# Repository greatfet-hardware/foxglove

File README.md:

# Foxglove
an advanced level shifting GreatFET neighbor

Required KiCad dependency:

https://github.com/greatscottgadgets/gsg-kicad-lib

If you are using git, the preferred way to install gsg-kicad-lib is to use the
submodule:

```
git submodule init && git submodule update
```

## Level Shifting

Foxglove is useful for interfacing with external targets at variety of I/O
voltage levels using a wide variety of protocols including SPI, I2C, UART, and
JTAG.  Level shifting on bank A is performed by the NXP 74LVCH1T45GW,125
supporting external voltages from 1.2 V to 5 V.  Level shifting on bank B pins
is performed by the Lattice LFE5U-12F-6BG256C (ECP5) FPGA supporting external
voltages from 1.2 V to 3.3 V.  Bank B also supports differential signals such
as LVDS.

## Pin Multiplexing

The FPGA allows Foxglove to switch arbitrary external wires to a variety of
pins on the Azalea's microcontroller in order to support a wide range of
microcontroller peripherals.

## Measurement and Probing

Foxglove provides the ability to connect an ADC, DAC, comparator, pull-up
resistor, or pull-down resistor to any of the pins on bank A.  This allows
analog measurement and probing of external targets.

Additionally, Foxglove is very useful for digital logic analysis and pattern
generation.

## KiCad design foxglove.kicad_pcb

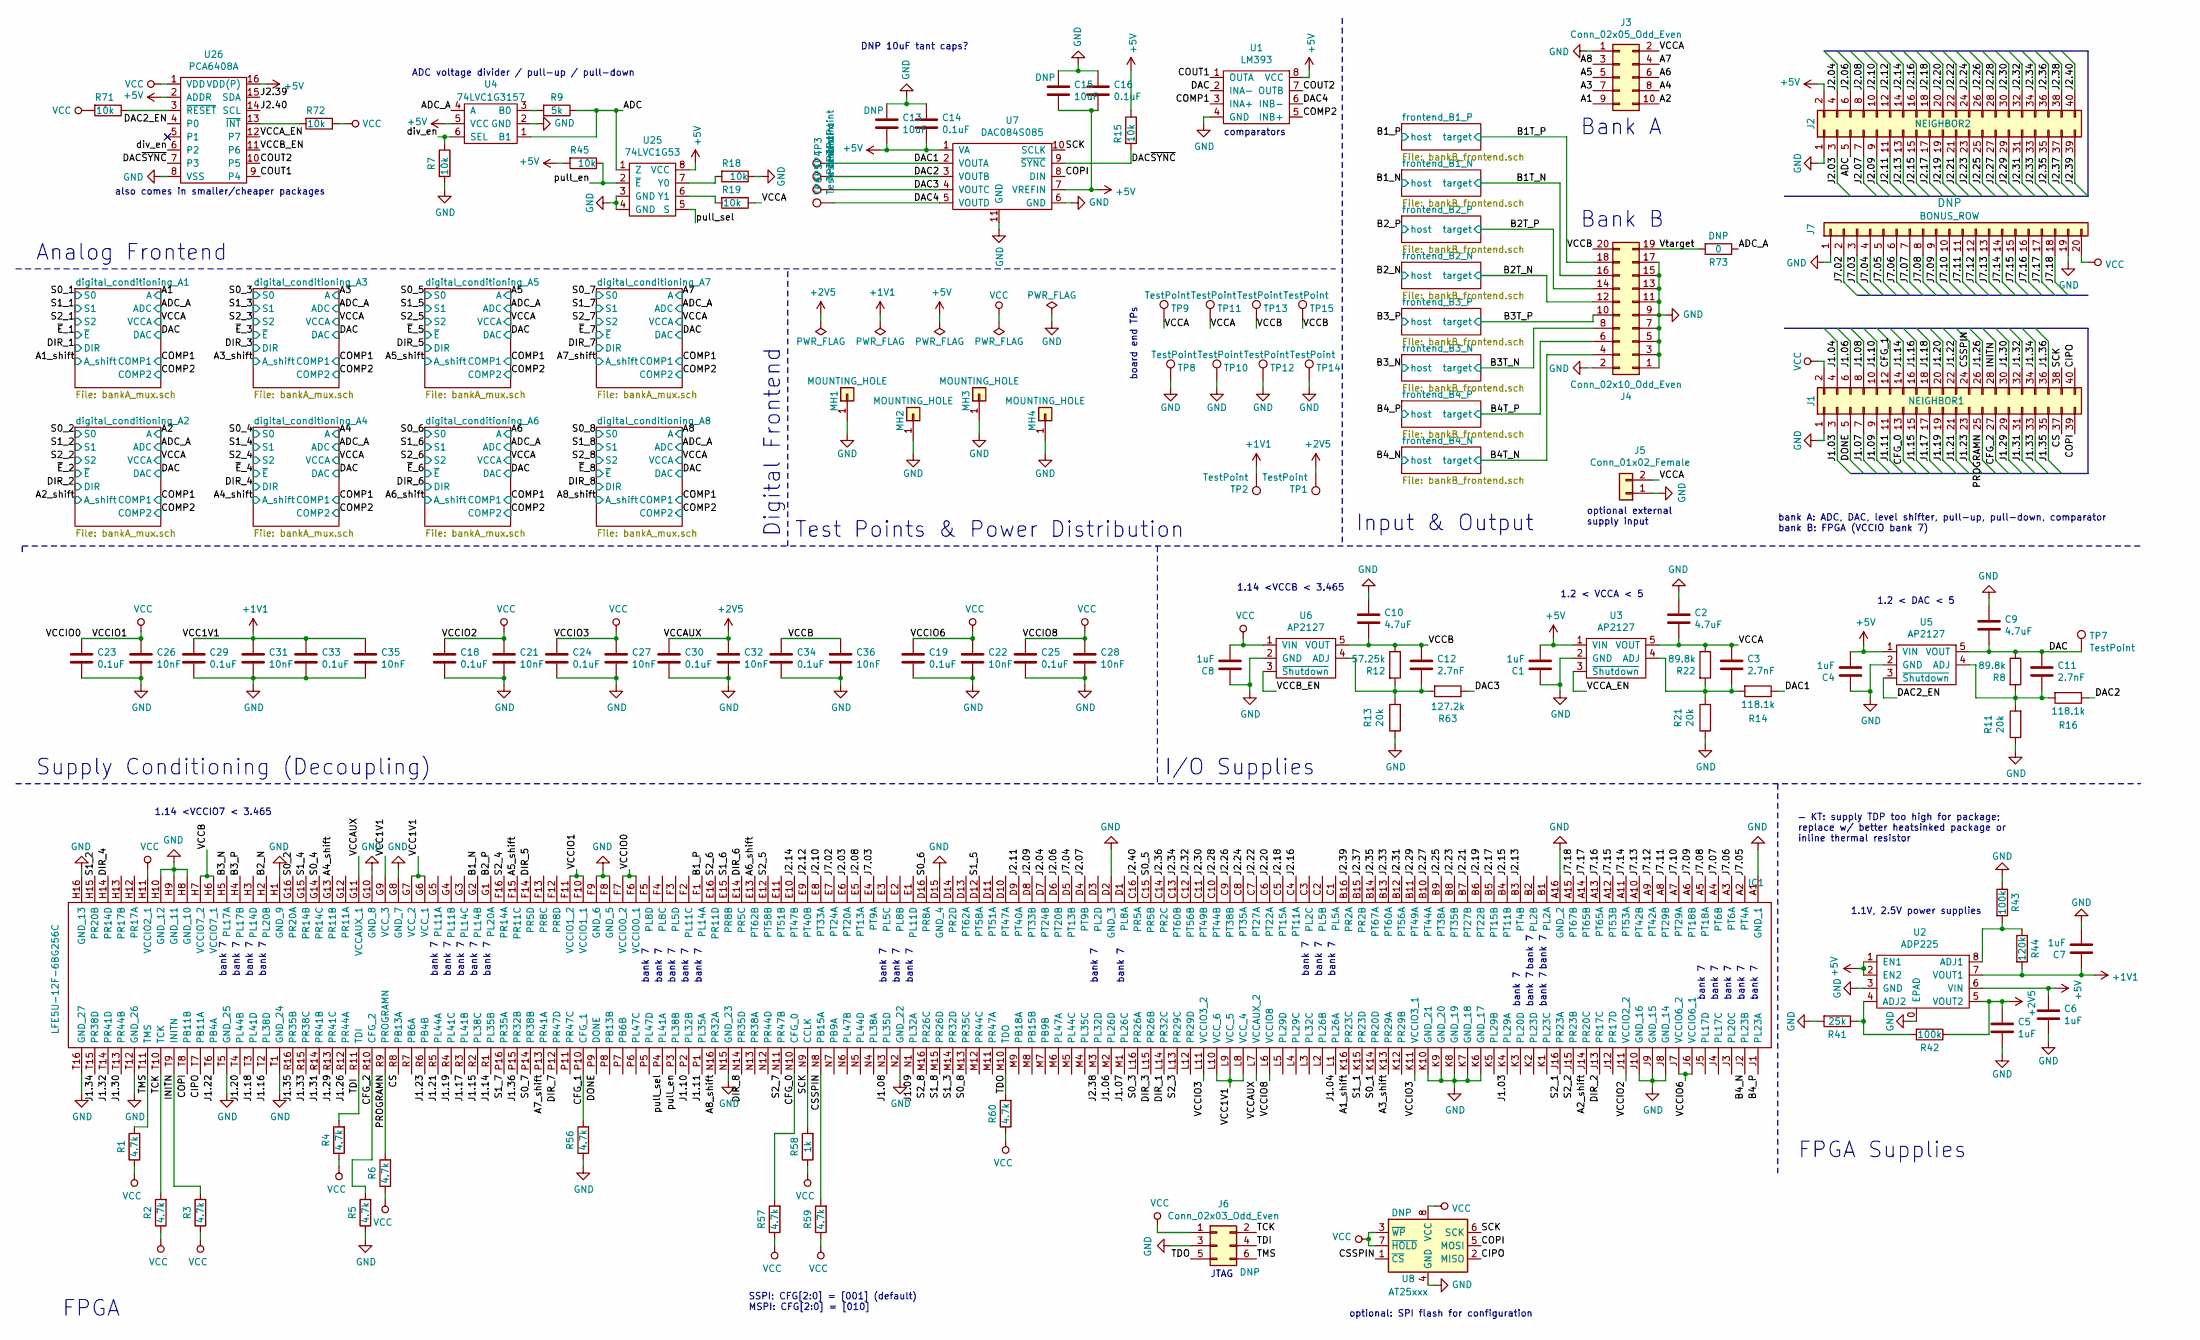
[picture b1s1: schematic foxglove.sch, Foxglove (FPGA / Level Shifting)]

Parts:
C1, C4, C5, C6, C7, C8: 1uF; 0402; Part Number GRT155R61E105KE01D
C2, C9, C10: 4.7uF; 0402; Part Number GRM155R61A475MEAAD
C3, C11, C12: 2.7nF; 0402; Part Number CC0402KRX7R9BB272
C13, C15: 10uF; 0603; Part Number F981A106MMA
C14, C16, C18, C19, C23, C24, C25, C29, C30, C33, C34: 0.1uF; 0402; Part Number EMK105BJ104KV-F
C21, C22, C26, C27, C28, C31, C32, C35, C36: 10nF; 0402; Part Number CL05B103KO5NNNC
IC1: LFE5U-12F-6BG256C; BGA256C80P16X16_1400X1400X170; Part Number LFE5U-12F-6BG256C; Mouser Part Number 842-LFE5U12F6BG256C
J1: NEIGHBOR1; HEADER-2x20; Part Number SSQ-120-23-G-D
J2: NEIGHBOR2; HEADER-2x20; Part Number SSQ-120-23-G-D
J3: Conn_02x05_Odd_Even; PinHeader_2x05_P2.54mm_Vertical; Part Number SBH11-PBPC-D05-RA-BK
J4: Conn_02x10_Odd_Even; PinHeader_2x10_P2.54mm_Vertical; Part Number SBH11-PBPC-D10-RA-BK
J5: Conn_01x02_Female; HEADER-1x2
J6: Conn_02x03_Odd_Even; PinHeader_2x03_P1.00mm_Vertical_SMD
J7: BONUS_ROW; HEADER-1x20; Part Number SSQ-120-23-G-S
MH1, MH2, MH3, MH4: MOUNTING_HOLE; HOLE126MIL-COPPER
R1, R2, R3, R4, R5, R6, R56, R57, R59, R60: 4.7k; 0402; Part Number RMCF0402JT4K70
R7, R15, R18, R19, R45, R71, R72: 10k; 0402; Part Number RMCF0402JT10K0
R8, R22: 89.8k; 0402; Part Number RMCF0402FT88K7
R9: 5k; 0402; Part Number PNM0402E5001BST1
R11, R13, R21: 20k; 0402; Part Number RMCF0402JT20K0
R12: 57.25k; 0402; Part Number RMCF0402FT57K6
R14, R16: 118.1k; 0402; Part Number RMCF0402FT118K
R41: 25k; 0402; Part Number PNM0402E2502BST1
R42, R43: 100k; 0402; Part Number RMCF0402JT100K
R44: 120k; 0402; Part Number RMCF0402FT120K
R58: 1k; 0402; Part Number RK73B1ETTP102J
R63: 127.2k; 0402; Part Number RMCF0402FT127K
R73: 0; 0402
TP1, TP2, TP3, TP4, TP5, TP6, TP7: TestPoint; TESTPOINT-50MIL
TP8, TP10, TP12, TP14: TestPoint; HEADER-1x1
TP9, TP11, TP13, TP15: TestPoint; HEADER-1x1-TESTPROBE
U1: LM393; SOIC8-154; Part Number LM393EDR2G
U2: ADP225; SON50P200X200X60-9N; Part Number ADP225ACPZ-R7
U3, U5, U6: AP2127; SOT-23-5; Part Number AP2127K-ADJTRG1
U4: 74LVC1G3157; SOT363; Part Number 74LVC1G3157DW-7
U7: DAC084S085; WSON-10-1EP_4x3mm_P0.5mm_EP2.2x2mm; Part Number DAC084S085CISDX/NOPB
U8: AT25xxx; SOIC8-154
U25: 74LVC1G53; VSSOP-8_2.3x2mm_P0.5mm; Part Number 74LVC1G53DC,125
U26: PCA6408A; TSSOP16; Part Number PCA6408APW,118

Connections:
+1V1: C7.1, C29.1, C31.1, C33.1, C35.1, IC1.G6 (VCC_1), IC1.G7 (VCC_2), IC1.G9 (VCC_3), IC1.L8 (VCC_4), IC1.L9 (VCC_5), IC1.L10 (VCC_6), R44.2, TP2.1, U2.7 (VOUT1)
+2V5: C5.1, C30.1, C32.1, IC1.G11 (VCCAUX_1), IC1.L7 (VCCAUX_2), R42.1, TP1.1, U2.5 (VOUT2)
+5V: C1.2, C4.2, C6.1, C13.1, C14.2, C15.1, C16.2, J2.2, R15.1, R45.2, U1.8 (VCC), U2.1 (EN1), U2.2 (EN2), U2.6 (VIN), U3.1 (VIN), U4.5 (VCC), U5.1 (VIN), U7.1 (VA), U7.7 (VREFIN), U25.8 (VCC), U26.2 (ADDR), U26.16 (VDD(P)); also elsewhere on the board
/A1_shift: IC1.K16 (PR23C); also elsewhere on the board
/A2: J3.10; also elsewhere on the board
/A2_shift: IC1.J14 (PR20C); also elsewhere on the board
/A3: J3.7; also elsewhere on the board
/A3_shift: IC1.K13 (PR29A); also elsewhere on the board
/A4_shift: IC1.G13 (PR11B); also elsewhere on the board
/A5: J3.5; also elsewhere on the board
/A5_shift: IC1.F15 (PR11C); also elsewhere on the board
/A6: J3.6; also elsewhere on the board
/A6_shift: IC1.E13 (PT62B); also elsewhere on the board
/A7: J3.4; also elsewhere on the board
/A7_shift: IC1.P13 (PR41A); also elsewhere on the board
/A8: J3.3; also elsewhere on the board
/A8_shift: IC1.N16 (PR32A); also elsewhere on the board
/ADC: J2.5, R9.1, U4.1 (B1), U25.1 (Z)
/ADC_A: R73.1, U4.4 (A); also elsewhere on the board
/B1T_N: J4.16; also elsewhere on the board
/B1T_P: J4.18; also elsewhere on the board
/B1_N: IC1.G2 (PL14B); also elsewhere on the board
/B1_P: IC1.F1 (PL14A); also elsewhere on the board
/B2T_N: J4.12; also elsewhere on the board
/B2T_P: J4.14; also elsewhere on the board
/B2_N: IC1.H2 (PL20B); also elsewhere on the board
/B2_P: IC1.G1 (PL20A); also elsewhere on the board
/B3T_N: J4.8; also elsewhere on the board
/B3T_P: J4.10; also elsewhere on the board
/B3_N: IC1.H5 (PL17A); also elsewhere on the board
/B3_P: IC1.H4 (PL17B); also elsewhere on the board
/B4T_N: J4.4; also elsewhere on the board
/B4T_P: J4.6; also elsewhere on the board
/B4_N: IC1.J2 (PL23B); also elsewhere on the board
/B4_P: IC1.J1 (PL23A); also elsewhere on the board
/CFG_0: IC1.N10 (CFG_0), J1.13, R57.2
/CFG_1: IC1.P10 (CFG_1), J1.12, R56.2
/CFG_2: IC1.R10 (CFG_2), J1.27, R5.2
/CIPO: IC1.T7 (PB11A), J1.40, U8.2 (MISO)
/COMP1: U1.3 (INA+); also elsewhere on the board
/COMP2: U1.5 (INB+); also elsewhere on the board
/COPI: IC1.T8 (PB11B), J1.39, U7.8 (DIN), U8.5 (MOSI)
/COUT1: U1.1 (OUTA), U26.9 (P4)
/COUT2: U1.7 (OUTB), U26.10 (P5)
/CS: IC1.R8 (PB13A), J1.37
/CSSPIN: IC1.N8 (PB15A), J1.24, R59.2, U8.1 (~CS)
/DAC: C9.2, C11.1, R8.1, TP7.1, U1.2 (INA-), U5.5 (VOUT); also elsewhere on the board
/DAC1: R14.1, TP3.1, U7.2 (VOUTA)
/DAC2: R16.1, TP4.1, U7.3 (VOUTB)
/DAC2_EN: U5.3 (~Shutdown~), U26.4 (P0)
/DAC3: R63.1, TP5.1, U7.4 (VOUTC)
/DAC4: TP6.1, U1.6 (INB-), U7.5 (VOUTD)
/DAC~SYNC~: R15.2, U7.9 (~SYNC~), U26.7 (P3)
/DIR_1: IC1.L14 (PR32C); also elsewhere on the board
/DIR_2: IC1.J13 (PR17C); also elsewhere on the board
/DIR_3: IC1.L15 (PR26B); also elsewhere on the board
/DIR_4: IC1.H14 (PR14D); also elsewhere on the board
/DIR_5: IC1.F14 (PR5D); also elsewhere on the board
/DIR_6: IC1.E14 (PR5C); also elsewhere on the board
/DIR_7: IC1.P12 (PR47D); also elsewhere on the board
/DIR_8: IC1.N14 (PR35D); also elsewhere on the board
/DONE: IC1.P9 (DONE), J1.5
/INITN: IC1.T9 (INITN), J1.28, R3.2
/J1.03: IC1.K4 (PL29A), J1.3
/J1.04: IC1.L1 (PL26A), J1.4
/J1.06: IC1.M2 (PL26D), J1.6
/J1.07: IC1.M1 (PL26C), J1.7
/J1.08: IC1.N3 (PL35D), J1.8
/J1.09: IC1.N1 (PL32A), J1.9
/J1.10: IC1.P2 (PL32B), J1.10
/J1.11: IC1.P1 (PL35A), J1.11
/J1.14: IC1.R1 (PL35B), J1.14
/J1.15: IC1.R2 (PL38C), J1.15
/J1.16: IC1.T2 (PL38D), J1.16
/J1.17: IC1.R3 (PL41B), J1.17
/J1.18: IC1.T3 (PL41D), J1.18
/J1.19: IC1.R4 (PL41C), J1.19
/J1.20: IC1.T4 (PL44B), J1.20
/J1.21: IC1.R5 (PL44A), J1.21
/J1.22: IC1.T6 (PB4A), J1.22
/J1.23: IC1.R6 (PB4B), J1.23
/J1.26: IC1.R12 (PR44A), J1.26
/J1.29: IC1.R13 (PR41C), J1.29
/J1.30: IC1.T13 (PR44B), J1.30
/J1.31: IC1.R14 (PR41B), J1.31
/J1.32: IC1.T14 (PR41D), J1.32
/J1.33: IC1.R15 (PR38C), J1.33
/J1.34: IC1.T15 (PR38D), J1.34
/J1.35: IC1.R16 (PR35B), J1.35
/J1.36: IC1.P15 (PR32B), J1.36
/J2.03: IC1.E6 (PT20A), J2.3
/J2.04: IC1.D7 (PT24B), J2.4
/J2.06: IC1.D6 (PT20B), J2.6
/J2.07: IC1.D4 (PT9B), J2.7
/J2.08: IC1.E5 (PT13A), J2.8
/J2.09: IC1.D8 (PT33B), J2.9
/J2.10: IC1.E8 (PT33A), J2.10
/J2.11: IC1.D9 (PT40A), J2.11
/J2.12: IC1.E9 (PT40B), J2.12
/J2.13: IC1.B3 (PT4B), J2.13
/J2.14: IC1.E10 (PT47B), J2.14
/J2.15: IC1.B4 (PT11B), J2.15
/J2.16: IC1.C4 (PT11A), J2.16
/J2.17: IC1.B5 (PT15B), J2.17
/J2.18: IC1.C5 (PT15A), J2.18
/J2.19: IC1.B6 (PT22B), J2.19
/J2.20: IC1.C6 (PT22A), J2.20
/J2.21: IC1.B7 (PT27B), J2.21
/J2.22: IC1.C7 (PT27A), J2.22
/J2.23: IC1.B8 (PT35B), J2.23
/J2.24: IC1.C8 (PT35A), J2.24
/J2.25: IC1.B9 (PT38A), J2.25
/J2.26: IC1.C9 (PT38B), J2.26
/J2.27: IC1.B10 (PT44A), J2.27
/J2.28: IC1.C10 (PT44B), J2.28
/J2.29: IC1.B11 (PT49A), J2.29
/J2.30: IC1.C11 (PT49B), J2.30
/J2.31: IC1.B12 (PT56A), J2.31
/J2.32: IC1.C12 (PT56B), J2.32
/J2.33: IC1.B13 (PT60A), J2.33
/J2.34: IC1.C13 (PT60B), J2.34
/J2.35: IC1.B14 (PT67A), J2.35
/J2.36: IC1.C14 (PR2C), J2.36
/J2.37: IC1.B15 (PR2B), J2.37
/J2.38: IC1.M3 (PL32D), J2.38
/J2.39: IC1.B16 (PR2A), J2.39, U26.15 (SDA)
/J2.40: IC1.C16 (PR5A), J2.40, U26.14 (SCL)
/J7.02: IC1.E7 (PT24A), J7.2
/J7.03: IC1.E4 (PT9A), J7.3
/J7.04: IC1.D5 (PT13B), J7.4
/J7.05: IC1.A2 (PT4A), J7.5
/J7.06: IC1.A3 (PT6A), J7.6
/J7.07: IC1.A4 (PT6B), J7.7
/J7.08: IC1.A5 (PT18A), J7.8
/J7.09: IC1.A6 (PT18B), J7.9
/J7.10: IC1.A7 (PT29A), J7.10
/J7.11: IC1.A8 (PT29B), J7.11
/J7.12: IC1.A9 (PT42A), J7.12
/J7.13: IC1.A10 (PT42B), J7.13
/J7.14: IC1.A11 (PT53A), J7.14
/J7.15: IC1.A12 (PT53B), J7.15
/J7.16: IC1.A13 (PT65A), J7.16
/J7.17: IC1.A14 (PT65B), J7.17
/J7.18: IC1.A15 (PT67B), J7.18
/PROGRAMN: IC1.R9 (PROGRAMN), J1.25, R6.2
/S0_1: IC1.K14 (PR20D); also elsewhere on the board
/S0_2: IC1.G16 (PR20A); also elsewhere on the board
/S0_3: IC1.L16 (PR26A); also elsewhere on the board
/S0_4: IC1.G14 (PR14C); also elsewhere on the board
/S0_5: IC1.C15 (PR5B); also elsewhere on the board
/S0_6: IC1.D16 (PR8A); also elsewhere on the board
/S0_7: IC1.P14 (PR38B); also elsewhere on the board
/S0_8: IC1.M13 (PR35C); also elsewhere on the board
/S1_1: IC1.K15 (PR23D); also elsewhere on the board
/S1_2: IC1.H15 (PR20B); also elsewhere on the board
/S1_3: IC1.M14 (PR32D); also elsewhere on the board
/S1_4: IC1.G15 (PR14B); also elsewhere on the board
/S1_5: IC1.D12 (PT58A); also elsewhere on the board
/S1_6: IC1.E15 (PR8B); also elsewhere on the board
/S1_7: IC1.P16 (PR35A); also elsewhere on the board
/S1_8: IC1.M15 (PR26D); also elsewhere on the board
/S2_1: IC1.J16 (PR23A); also elsewhere on the board
/S2_2: IC1.J15 (PR23B); also elsewhere on the board
/S2_3: IC1.L13 (PR29C); also elsewhere on the board
/S2_4: IC1.F16 (PR14A); also elsewhere on the board
/S2_5: IC1.E12 (PT58B); also elsewhere on the board
/S2_6: IC1.E16 (PR11D); also elsewhere on the board
/S2_7: IC1.N11 (PR47B); also elsewhere on the board
/S2_8: IC1.M16 (PR26C); also elsewhere on the board
/SCK: IC1.N9 (CCLK), J1.38, R58.2, U7.10 (SCLK), U8.6 (SCK)
/TCK: IC1.T10 (TCK), J6.2, R2.2
/TDI: IC1.R11 (TDI), J6.4, R4.2
/TDO: IC1.M10 (TDO), J6.5, R60.2
/TMS: IC1.T11 (TMS), J6.6, R1.2
/VCCA: C2.2, C3.1, J3.2, J5.2, R19.1, R22.1, TP9.1, TP11.1, U3.5 (VOUT); also elsewhere on the board
/VCCA_EN: U3.3 (~Shutdown~), U26.12 (P7)
/VCCB: C10.2, C12.1, C34.1, C36.1, IC1.H6 (VCCIO7_1), IC1.H7 (VCCIO7_2), J4.20, R12.1, TP13.1, TP15.1, U6.5 (VOUT)
/VCCB_EN: U6.3 (~Shutdown~), U26.11 (P6)
/Vtarget: J4.19, R73.2
/div_en: R7.1, U4.6 (SEL), U26.6 (P2)
/pull_en: IC1.P3 (PL38B), R45.1, U25.2 (~E~)
/pull_sel: IC1.P4 (PL41A), U25.5 (S)
GND: C1.1, C2.1, C4.1, C5.2, C6.2, C7.2, C8.1, C9.1, C10.1, C13.2, C14.1, C15.2, C16.1, C18.2, C19.2, C21.2, C22.2, C23.2, C24.2, C25.2, C26.2, C27.2, C28.2, C29.2, C30.2, C31.2, C32.2, C33.2, C34.2, C35.2, C36.2, IC1.A1 (GND_1), IC1.A16 (GND_2), IC1.D2 (GND_3), IC1.D15 (GND_4), IC1.F8 (GND_5), IC1.F9 (GND_6), IC1.G8 (GND_7), IC1.G10 (GND_8), IC1.H1 (GND_9), IC1.H8 (GND_10), IC1.H9 (GND_11), IC1.H10 (GND_12), IC1.H16 (GND_13), IC1.J8 (GND_14), IC1.J9 (GND_15), IC1.J10 (GND_16), IC1.K6 (GND_17), IC1.K7 (GND_18), IC1.K8 (GND_19), IC1.K9 (GND_20), IC1.K10 (GND_21), IC1.N2 (GND_22), IC1.N15 (GND_23), IC1.T1 (GND_24), IC1.T5 (GND_25), IC1.T12 (GND_26), IC1.T16 (GND_27), J1.1, J2.1, J3.1, J4.1, J4.2, J4.3, J4.5, J4.7, J4.9, J4.11, J4.13, J4.15, J4.17, J5.1, J6.3, J7.1, J7.19, MH1.1, MH2.1, MH3.1, MH4.1, R5.1, R7.2, R11.1, R13.1, R18.1, R21.1, R41.2, R43.1, R56.1, TP8.1, TP10.1, TP12.1, TP14.1, U1.4 (GND), U2.0 (EPAD), U2.3 (GND), U3.2 (GND), U4.2 (GND), U5.2 (GND), U6.2 (GND), U7.6 (GND), U7.11 (GND), U8.4 (GND), U25.3 (GND), U25.4 (GND), U26.8 (VSS); also elsewhere on the board
unnamed: C3.2, R14.2, R21.2, R22.2, U3.4 (ADJ)
unnamed: C11.2, R8.2, R11.2, R16.2, U5.4 (ADJ)
unnamed: C12.2, R12.2, R13.2, R63.2, U6.4 (ADJ)
unnamed: R9.2, U4.3 (B0)
unnamed: R18.2, U25.7 (Y0)
unnamed: R19.2, U25.6 (Y1)
unnamed: R41.1, R42.2, U2.4 (ADJ2)
unnamed: R43.2, R44.1, U2.8 (ADJ1)
unnamed: R71.1, U26.3 (~RESET~)
unnamed: R72.2, U26.13 (~INT~)
VCC: C8.2, C18.1, C19.1, C21.1, C22.1, C23.1, C24.1, C25.1, C26.1, C27.1, C28.1, IC1.F6 (VCCIO0_1), IC1.F7 (VCCIO0_2), IC1.F10 (VCCIO1_1), IC1.F11 (VCCIO1_2), IC1.H11 (VCCIO2_1), IC1.J6 (VCCIO6_1), IC1.J7 (VCCIO6_2), IC1.J11 (VCCIO2_2), IC1.K11 (VCCIO3_1), IC1.L6 (VCCIO8), IC1.L11 (VCCIO3_2), J1.2, J6.1, J7.20, R1.1, R2.1, R3.1, R4.1, R6.1, R57.1, R58.1, R59.1, R60.1, R71.2, R72.1, U6.1 (VIN), U8.3 (~WP), U8.7 (~HOLD), U8.8 (VCC), U26.1 (VDD); also elsewhere on the board

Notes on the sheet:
bank A: ADC, DAC, level shifter, pull-up, pull-down, comparator bank B: FPGA (VCCIO bank 7)
comparators
optional external supply input
JTAG
SSPI: CFG[2:0] = [001] (default) MSPI: CFG[2:0] = [010]
bank 7
1.14 <VCCIO7 < 3.465
1.2 < VCCA < 5
1.2 < DAC < 5
1.14 <VCCB < 3.465
ADC voltage divider / pull-up / pull-down
1.1V, 2.5V power supplies
optional: SPI flash for configuration
also comes in smaller/cheaper packages
DNP 10uF tant caps?
Analog Frontend
Test Points & Power Distribution
Supply Conditioning (Decoupling)
I/O Supplies
Input & Output
Digital Frontend
FPGA
FPGA Supplies
— KT: supply TDP too high for package; replace w/ better heatsinked package or inline thermal resistor
board end TPs
Bank B
Bank A

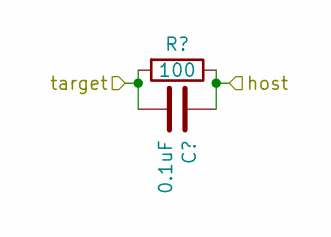
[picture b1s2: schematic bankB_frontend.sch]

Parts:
C17: 0.1uF; 0402; Part Number EMK105BJ104KV-F
R10: 100; 0402; Part Number RMCF0402JT100R

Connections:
/B1T_P: C17.2, R10.2; also elsewhere on the board
/B1_P: C17.1, R10.1; also elsewhere on the board

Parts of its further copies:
C44, C45, C46, C47, C48, C49, C50: 0.1uF; 0402; Part Number EMK105BJ104KV-F
R64, R65, R66, R67, R68, R69, R70: 100; 0402; Part Number RMCF0402JT100R

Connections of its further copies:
/B1T_N: C44.2, R64.2; also elsewhere on the board
/B1_N: C44.1, R64.1; also elsewhere on the board
/B2T_N: C46.2, R66.2; also elsewhere on the board
/B2T_P: C45.2, R65.2; also elsewhere on the board
/B2_N: C46.1, R66.1; also elsewhere on the board
/B2_P: C45.1, R65.1; also elsewhere on the board
/B3T_N: C48.2, R68.2; also elsewhere on the board
/B3T_P: C47.2, R67.2; also elsewhere on the board
/B3_N: C48.1, R68.1; also elsewhere on the board
/B3_P: C47.1, R67.1; also elsewhere on the board
/B4T_N: C50.2, R70.2; also elsewhere on the board
/B4T_P: C49.2, R69.2; also elsewhere on the board
/B4_N: C50.1, R70.1; also elsewhere on the board
/B4_P: C49.1, R69.1; also elsewhere on the board

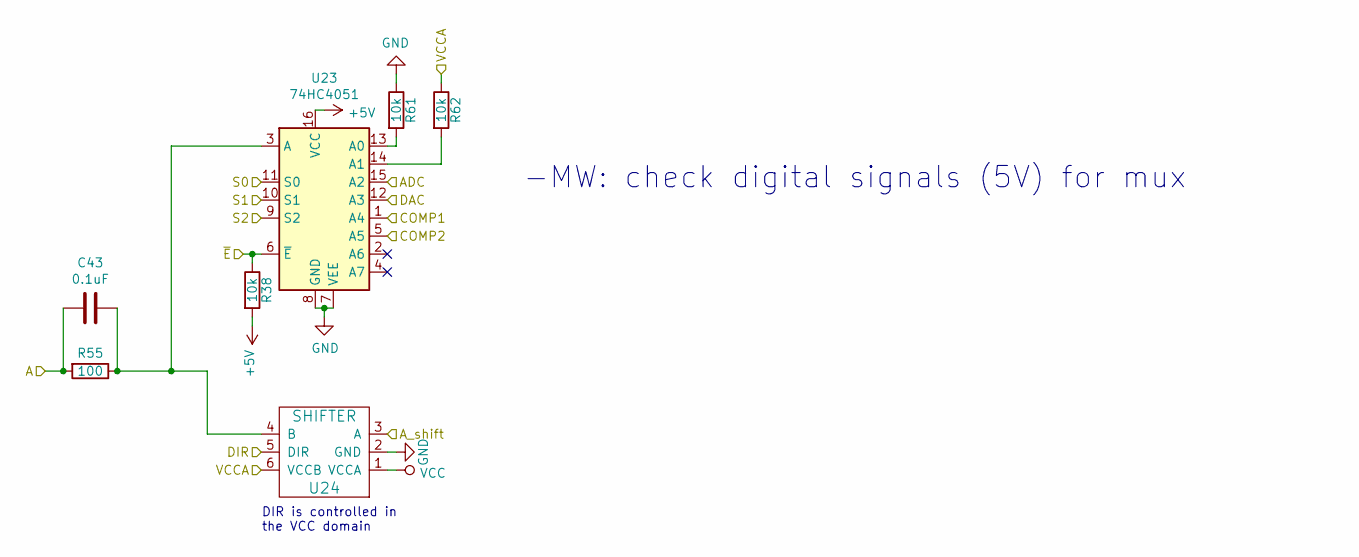
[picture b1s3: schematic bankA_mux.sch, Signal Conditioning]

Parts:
C39: 0.1uF; 0402; Part Number EMK105BJ104KV-F
R17, R24, R25: 10k; 0402; Part Number RMCF0402JT10K0
R48: 100; 0402; Part Number RMCF0402JT100R
U9: 74HC4051; SOT-763-1; Part Number 74HC4051BQ,115
U10: SHIFTER; SOT363; Part Number 74LVCH1T45GW,125

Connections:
+5V: R17.2, U9.16 (VCC); also elsewhere on the board
/A1_shift: U10.3 (A); also elsewhere on the board
/ADC_A: U9.15 (A2); also elsewhere on the board
/COMP1: U9.1 (A4); also elsewhere on the board
/COMP2: U9.5 (A5); also elsewhere on the board
/DAC: U9.12 (A3); also elsewhere on the board
/DIR_1: U10.5 (DIR); also elsewhere on the board
/S0_1: U9.11 (S0); also elsewhere on the board
/S1_1: U9.10 (S1); also elsewhere on the board
/S2_1: U9.9 (S2); also elsewhere on the board
/VCCA: R25.1, U10.6 (VCCB); also elsewhere on the board
/~E~_1: R17.1, U9.6 (~E)
GND: R24.1, U9.7 (VEE), U9.8 (GND), U10.2 (GND); also elsewhere on the board
unnamed: R24.2, U9.13 (A0)
unnamed: R25.2, U9.14 (A1)
VCC: U10.1 (VCCA); also elsewhere on the board

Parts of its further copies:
C20, C37, C38, C40, C41, C42, C43: 0.1uF; 0402; Part Number EMK105BJ104KV-F
R20, R23, R26, R27, R28, R29, R30, R31, R32, R33, R34, R35, R36, R37, R38, R39, R40, R46, R47, R61, R62: 10k; 0402; Part Number RMCF0402JT10K0
R49, R50, R51, R52, R53, R54, R55: 100; 0402; Part Number RMCF0402JT100R
U11, U13, U15, U17, U19, U21, U23: 74HC4051; SOT-763-1; Part Number 74HC4051BQ,115
U12, U14, U16, U18, U20, U22, U24: SHIFTER; SOT363; Part Number 74LVCH1T45GW,125

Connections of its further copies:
+5V: R20.2, R23.2, R26.2, R29.2, R32.2, R35.2, R38.2, U11.16 (VCC), U13.16 (VCC), U15.16 (VCC), U17.16 (VCC), U19.16 (VCC), U21.16 (VCC), U23.16 (VCC); also elsewhere on the board
/A2: C37.1, R49.2; also elsewhere on the board
/A2_shift: U12.3 (A); also elsewhere on the board
/A3: C38.1, R50.2; also elsewhere on the board
/A3_shift: U14.3 (A); also elsewhere on the board
/A4_shift: U16.3 (A); also elsewhere on the board
/A5: C40.1, R52.2; also elsewhere on the board
/A5_shift: U18.3 (A); also elsewhere on the board
/A6: C41.1, R53.2; also elsewhere on the board
/A6_shift: U20.3 (A); also elsewhere on the board
/A7: C42.1, R54.2; also elsewhere on the board
/A7_shift: U22.3 (A); also elsewhere on the board
/A8: C43.1, R55.2; also elsewhere on the board
/A8_shift: U24.3 (A); also elsewhere on the board
/ADC_A: U11.15 (A2), U13.15 (A2), U15.15 (A2), U17.15 (A2), U19.15 (A2), U21.15 (A2), U23.15 (A2); also elsewhere on the board
/COMP1: U11.1 (A4), U13.1 (A4), U15.1 (A4), U17.1 (A4), U19.1 (A4), U21.1 (A4), U23.1 (A4); also elsewhere on the board
/COMP2: U11.5 (A5), U13.5 (A5), U15.5 (A5), U17.5 (A5), U19.5 (A5), U21.5 (A5), U23.5 (A5); also elsewhere on the board
/DAC: U11.12 (A3), U13.12 (A3), U15.12 (A3), U17.12 (A3), U19.12 (A3), U21.12 (A3), U23.12 (A3); also elsewhere on the board
/DIR_2: U12.5 (DIR); also elsewhere on the board
/DIR_3: U14.5 (DIR); also elsewhere on the board
/DIR_4: U16.5 (DIR); also elsewhere on the board
/DIR_5: U18.5 (DIR); also elsewhere on the board
/DIR_6: U20.5 (DIR); also elsewhere on the board
/DIR_7: U22.5 (DIR); also elsewhere on the board
/DIR_8: U24.5 (DIR); also elsewhere on the board
/S0_2: U11.11 (S0); also elsewhere on the board
/S0_3: U13.11 (S0); also elsewhere on the board
/S0_4: U15.11 (S0); also elsewhere on the board
/S0_5: U17.11 (S0); also elsewhere on the board
/S0_6: U19.11 (S0); also elsewhere on the board
/S0_7: U21.11 (S0); also elsewhere on the board
/S0_8: U23.11 (S0); also elsewhere on the board
/S1_2: U11.10 (S1); also elsewhere on the board
/S1_3: U13.10 (S1); also elsewhere on the board
/S1_4: U15.10 (S1); also elsewhere on the board
/S1_5: U17.10 (S1); also elsewhere on the board
/S1_6: U19.10 (S1); also elsewhere on the board
/S1_7: U21.10 (S1); also elsewhere on the board
/S1_8: U23.10 (S1); also elsewhere on the board
/S2_2: U11.9 (S2); also elsewhere on the board
/S2_3: U13.9 (S2); also elsewhere on the board
/S2_4: U15.9 (S2); also elsewhere on the board
/S2_5: U17.9 (S2); also elsewhere on the board
/S2_6: U19.9 (S2); also elsewhere on the board
/S2_7: U21.9 (S2); also elsewhere on the board
/S2_8: U23.9 (S2); also elsewhere on the board
/VCCA: R28.1, R31.1, R34.1, R37.1, R40.1, R47.1, R62.1, U12.6 (VCCB), U14.6 (VCCB), U16.6 (VCCB), U18.6 (VCCB), U20.6 (VCCB), U22.6 (VCCB), U24.6 (VCCB); also elsewhere on the board
/~E~_2: R20.1, U11.6 (~E)
/~E~_3: R23.1, U13.6 (~E)
/~E~_4: R26.1, U15.6 (~E)
/~E~_5: R29.1, U17.6 (~E)
/~E~_6: R32.1, U19.6 (~E)
/~E~_7: R35.1, U21.6 (~E)
/~E~_8: R38.1, U23.6 (~E)
GND: R27.1, R30.1, R33.1, R36.1, R39.1, R46.1, R61.1, U11.7 (VEE), U11.8 (GND), U12.2 (GND), U13.7 (VEE), U13.8 (GND), U14.2 (GND), U15.7 (VEE), U15.8 (GND), U16.2 (GND), U17.7 (VEE), U17.8 (GND), U18.2 (GND), U19.7 (VEE), U19.8 (GND), U20.2 (GND), U21.7 (VEE), U21.8 (GND), U22.2 (GND), U23.7 (VEE), U23.8 (GND), U24.2 (GND); also elsewhere on the board
unnamed: C37.2, R49.1, U11.3 (A), U12.4 (B)
unnamed: C38.2, R50.1, U13.3 (A), U14.4 (B)
unnamed: C40.2, R52.1, U17.3 (A), U18.4 (B)
unnamed: C41.2, R53.1, U19.3 (A), U20.4 (B)
unnamed: C42.2, R54.1, U21.3 (A), U22.4 (B)
unnamed: C43.2, R55.1, U23.3 (A), U24.4 (B)
unnamed: R27.2, U11.13 (A0)
unnamed: R28.2, U11.14 (A1)
unnamed: R30.2, U13.13 (A0)
unnamed: R31.2, U13.14 (A1)
unnamed: R33.2, U15.13 (A0)
unnamed: R34.2, U15.14 (A1)
unnamed: R36.2, U17.13 (A0)
unnamed: R37.2, U17.14 (A1)
unnamed: R39.2, U19.13 (A0)
unnamed: R40.2, U19.14 (A1)
unnamed: R46.2, U21.13 (A0)
unnamed: R47.2, U21.14 (A1)
unnamed: R61.2, U23.13 (A0)
unnamed: R62.2, U23.14 (A1)
VCC: U12.1 (VCCA), U14.1 (VCCA), U16.1 (VCCA), U18.1 (VCCA), U20.1 (VCCA), U22.1 (VCCA), U24.1 (VCCA); also elsewhere on the board

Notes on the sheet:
DIR is controlled in the VCC domain
-MW: check digital signals (5V) for mux

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
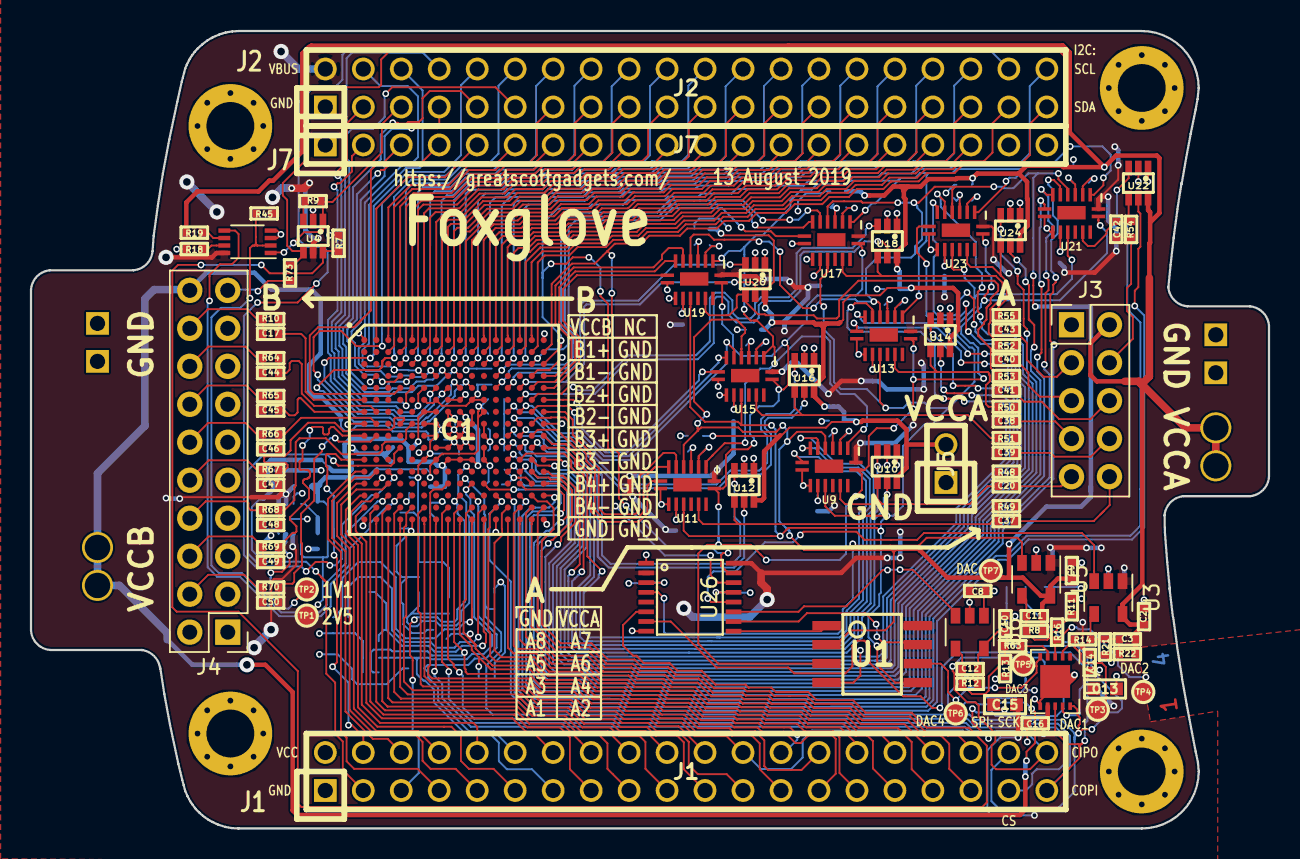
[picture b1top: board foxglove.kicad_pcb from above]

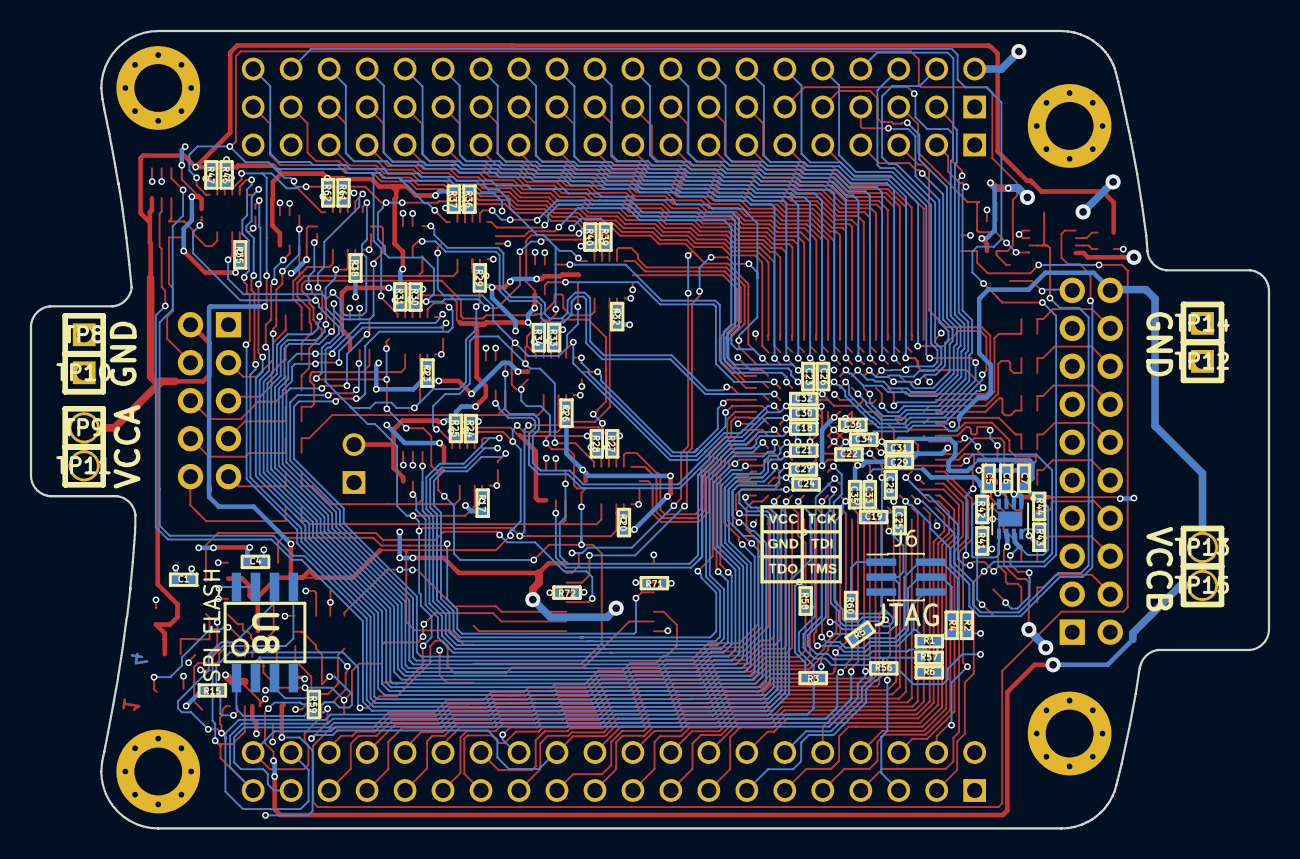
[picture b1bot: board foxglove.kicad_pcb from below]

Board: 4 copper layers, 82.8 x 53.3 mm, 176 parts (76 on the bottom side), 228 nets.

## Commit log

2019-03-27 Added iCE40-HX8K-CT256 to schematic, began signal routing.
2019-03-29 Foxglove: Routed signals to FPGA and set up bank A multiplexors
2019-03-29 Continued work on Foxglove schematic (added bypass caps, selected footprints, etc.). Placed parts on PCB.
2019-04-04 Routed FPGA connections to J2 connector
2019-04-05 Foxglove: Routed FPGA to J1 header
2019-04-09 Added design notes
2019-04-16 Added switch for pull-up/down in parallel with ADC
2019-04-19 Added LFE5U-12F-6BG256C to schematic
2019-04-24 Routed FPGA power and JTAG connections
2019-05-01 Made FPGA connections to greatfet headers
2019-05-02 Started routing connections to J2 and J7
2019-05-03 Routed all greatfet headers to FPGA
2019-05-07 Changed DAC controlled LDO
2019-05-13 Connected bank B to VCCIO7 pins, switched out voltage regulators
2019-05-14 Added DAC2 LDO
2019-05-14 Added LDOs for DAC and VCCB
2019-05-22 Routed bank B to FPGA VCCIO7, added bypass caps
2019-05-22 Routed ADC/DAC and FPGA passives
2019-05-23 Corrected DAC caps, added DAC test points
2019-05-27 split foxglove into separate repository
2019-05-28 Began routing bank A
2019-05-29 remove and ignore generated .net files
2019-05-29 remove generated .xml file
2019-05-29 replace full paths with relative paths
2019-06-04 removed old sub-level schematics 'shifters' and 'power_supplies' and added new schematic 'bankA_mux'
2019-06-04 Fixed sym-lib-table and continued routing bank A
2019-06-19 Changed headers for bank A and B, combined ADC voltage divider / pull-ups
2019-06-20 Completed routing of new connectors.
2019-06-21 Completed Bank A mux routing.
2019-06-25 Added I2C IO expander
2019-06-26 Completed routing
2019-07-02 Matched path length of bank B differential pairs
2019-07-02 Changed bank A footprint and rearranged silkscreen
2019-07-08 Added silkscreen tables for banks and completed BOM data
2019-07-23 Corrected FPGA footprint
2019-07-30 Improved silkscreen table visibility and changed board edge cuts to support right-angle connectors
2019-08-14 Flipped J4 footprint
2019-09-04 schematic: cleanup and squish onto a page
2019-09-06 move information from greatfet wiki to README
2020-07-03 adopt OSHWA convention for SPI signal names https://www.oshwa.org/a-resolution-to-redefine-spi-signal-names

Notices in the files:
foxglove.sch:
Copyright 2019 Great Scott Gadgets
License: GPL v2
foxglove/foxglove.sch:
Copyright 2015 Michael Ossmann
